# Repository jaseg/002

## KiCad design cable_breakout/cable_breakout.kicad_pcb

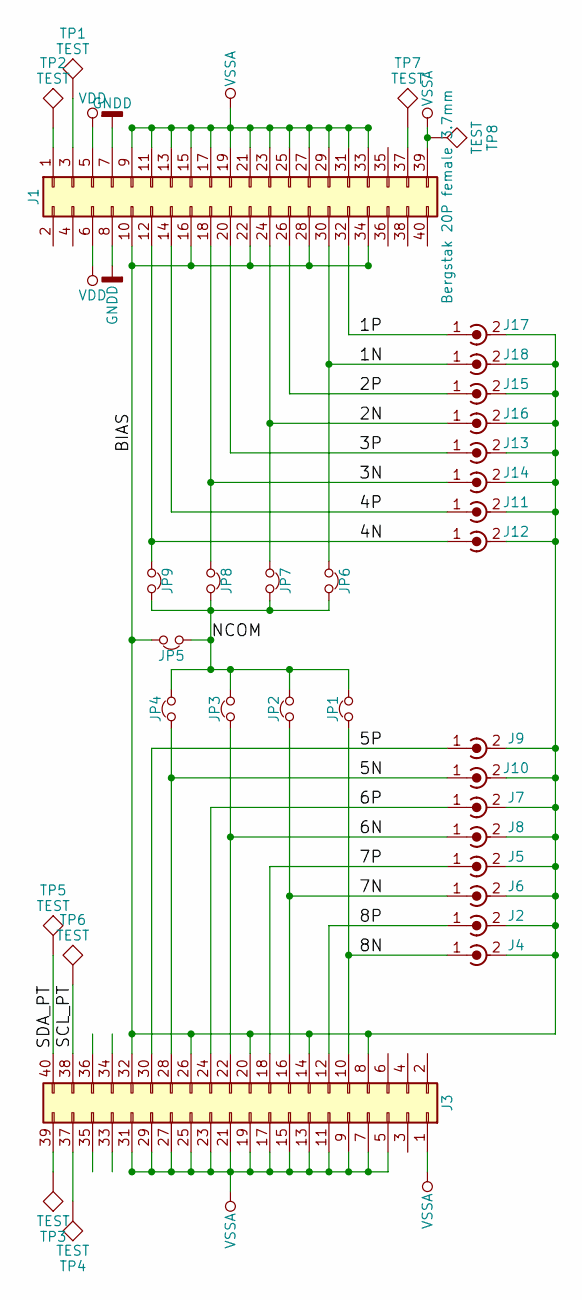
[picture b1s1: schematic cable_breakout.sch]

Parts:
J1: Bergstak 20P female 3.7mm; bergstak_plug_2x20_male; Mfg PN 10144517-041802LF; Digikey PN 609-5429-1-ND
J2, J4, J5, J6, J7, J8, J9, J10, J11, J12, J13, J14, J15, J16, J17, J18: Conn_Coaxial_Power; rg178_coax_solder_pad
J3: Conn_02x20_Odd_Even; bergstak_plug_2x20_male; Mfg PN 10144517-041802LF; Digikey PN 609-5429-1-ND
JP1, JP2, JP3, JP4, JP5, JP6, JP7, JP8, JP9: Jumper_NC_Small; solder_jumper_2pin
TP1, TP2, TP3, TP4, TP5, TP6, TP7, TP8: TEST; patch_pad

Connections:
/1N: J1.30, J18.1 (In), JP6.1
/1P: J1.32, J17.1 (In)
/2N: J1.24, J16.1 (In), JP7.1
/2P: J1.26, J15.1 (In)
/3N: J1.18, J14.1 (In), JP8.1
/3P: J1.20, J13.1 (In)
/4N: J1.12, J12.1 (In), JP9.1
/4P: J1.14, J11.1 (In)
/5N: J3.28, J10.1 (In), JP4.1
/5P: J3.30, J9.1 (In)
/6N: J3.22, J8.1 (In), JP3.1
/6P: J3.24, J7.1 (In)
/7N: J3.16, J6.1 (In), JP2.1
/7P: J3.18, J5.1 (In)
/8N: J3.10, J4.1 (In), JP1.1
/8P: J2.1 (In), J3.12
/BIAS: J1.10, J1.16, J1.22, J1.28, J1.34, J2.2 (Ext), J3.8, J3.14, J3.20, J3.26, J3.32, J4.2 (Ext), J5.2 (Ext), J6.2 (Ext), J7.2 (Ext), J8.2 (Ext), J9.2 (Ext), J10.2 (Ext), J11.2 (Ext), J12.2 (Ext), J13.2 (Ext), J14.2 (Ext), J15.2 (Ext), J16.2 (Ext), J17.2 (Ext), J18.2 (Ext), JP5.2
/NCOM: JP1.2, JP2.2, JP3.2, JP4.2, JP5.1, JP6.2, JP7.2, JP8.2, JP9.2
/SCL_PT: J3.38, TP6.1
/SDA_PT: J3.40, TP5.1
GNDD: J1.7, J1.8; also elsewhere on the board
unnamed: J1.1, TP2.1
unnamed: J1.3, TP1.1
unnamed: J1.37, TP7.1
unnamed: J3.37, TP4.1
unnamed: J3.39, TP3.1
VDD: J1.5, J1.6; also elsewhere on the board
VSSA: J1.9, J1.11, J1.13, J1.15, J1.17, J1.19, J1.21, J1.23, J1.25, J1.27, J1.29, J1.31, J1.33, J1.39, J3.1, J3.5, J3.7, J3.9, J3.11, J3.13, J3.15, J3.17, J3.19, J3.21, J3.23, J3.25, J3.27, J3.29, J3.31, TP8.1

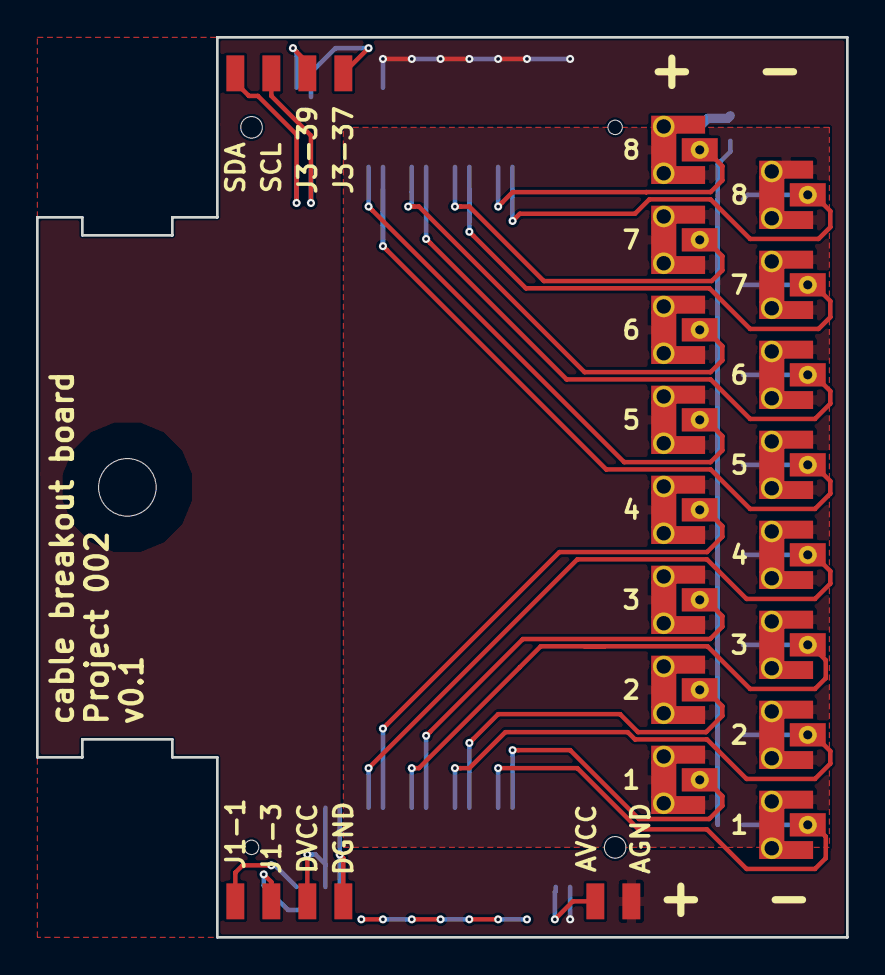
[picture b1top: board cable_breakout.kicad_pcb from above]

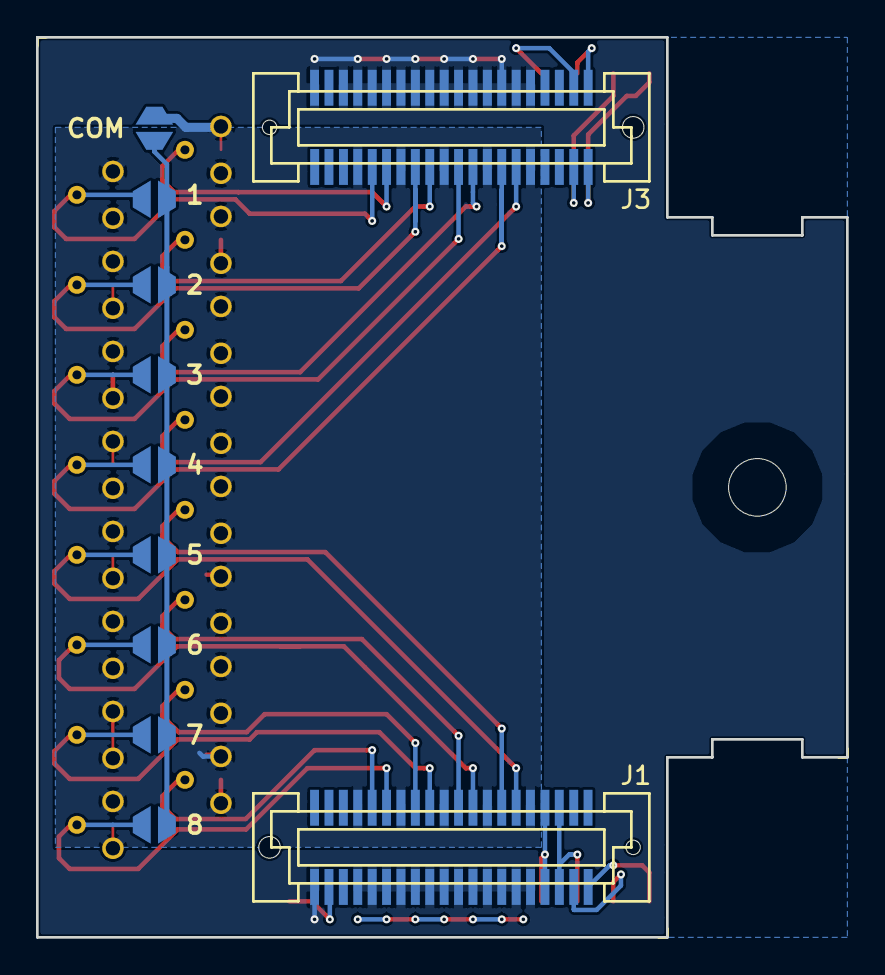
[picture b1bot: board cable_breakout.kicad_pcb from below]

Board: 2 copper layers, 45.0 x 50.0 mm, 37 parts (11 on the bottom side), 28 nets.

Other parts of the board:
TP9, TP10: TEST; patch_pad

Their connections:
GNDD: TP9.1; also elsewhere on the board
VDD: TP10.1; also elsewhere on the board

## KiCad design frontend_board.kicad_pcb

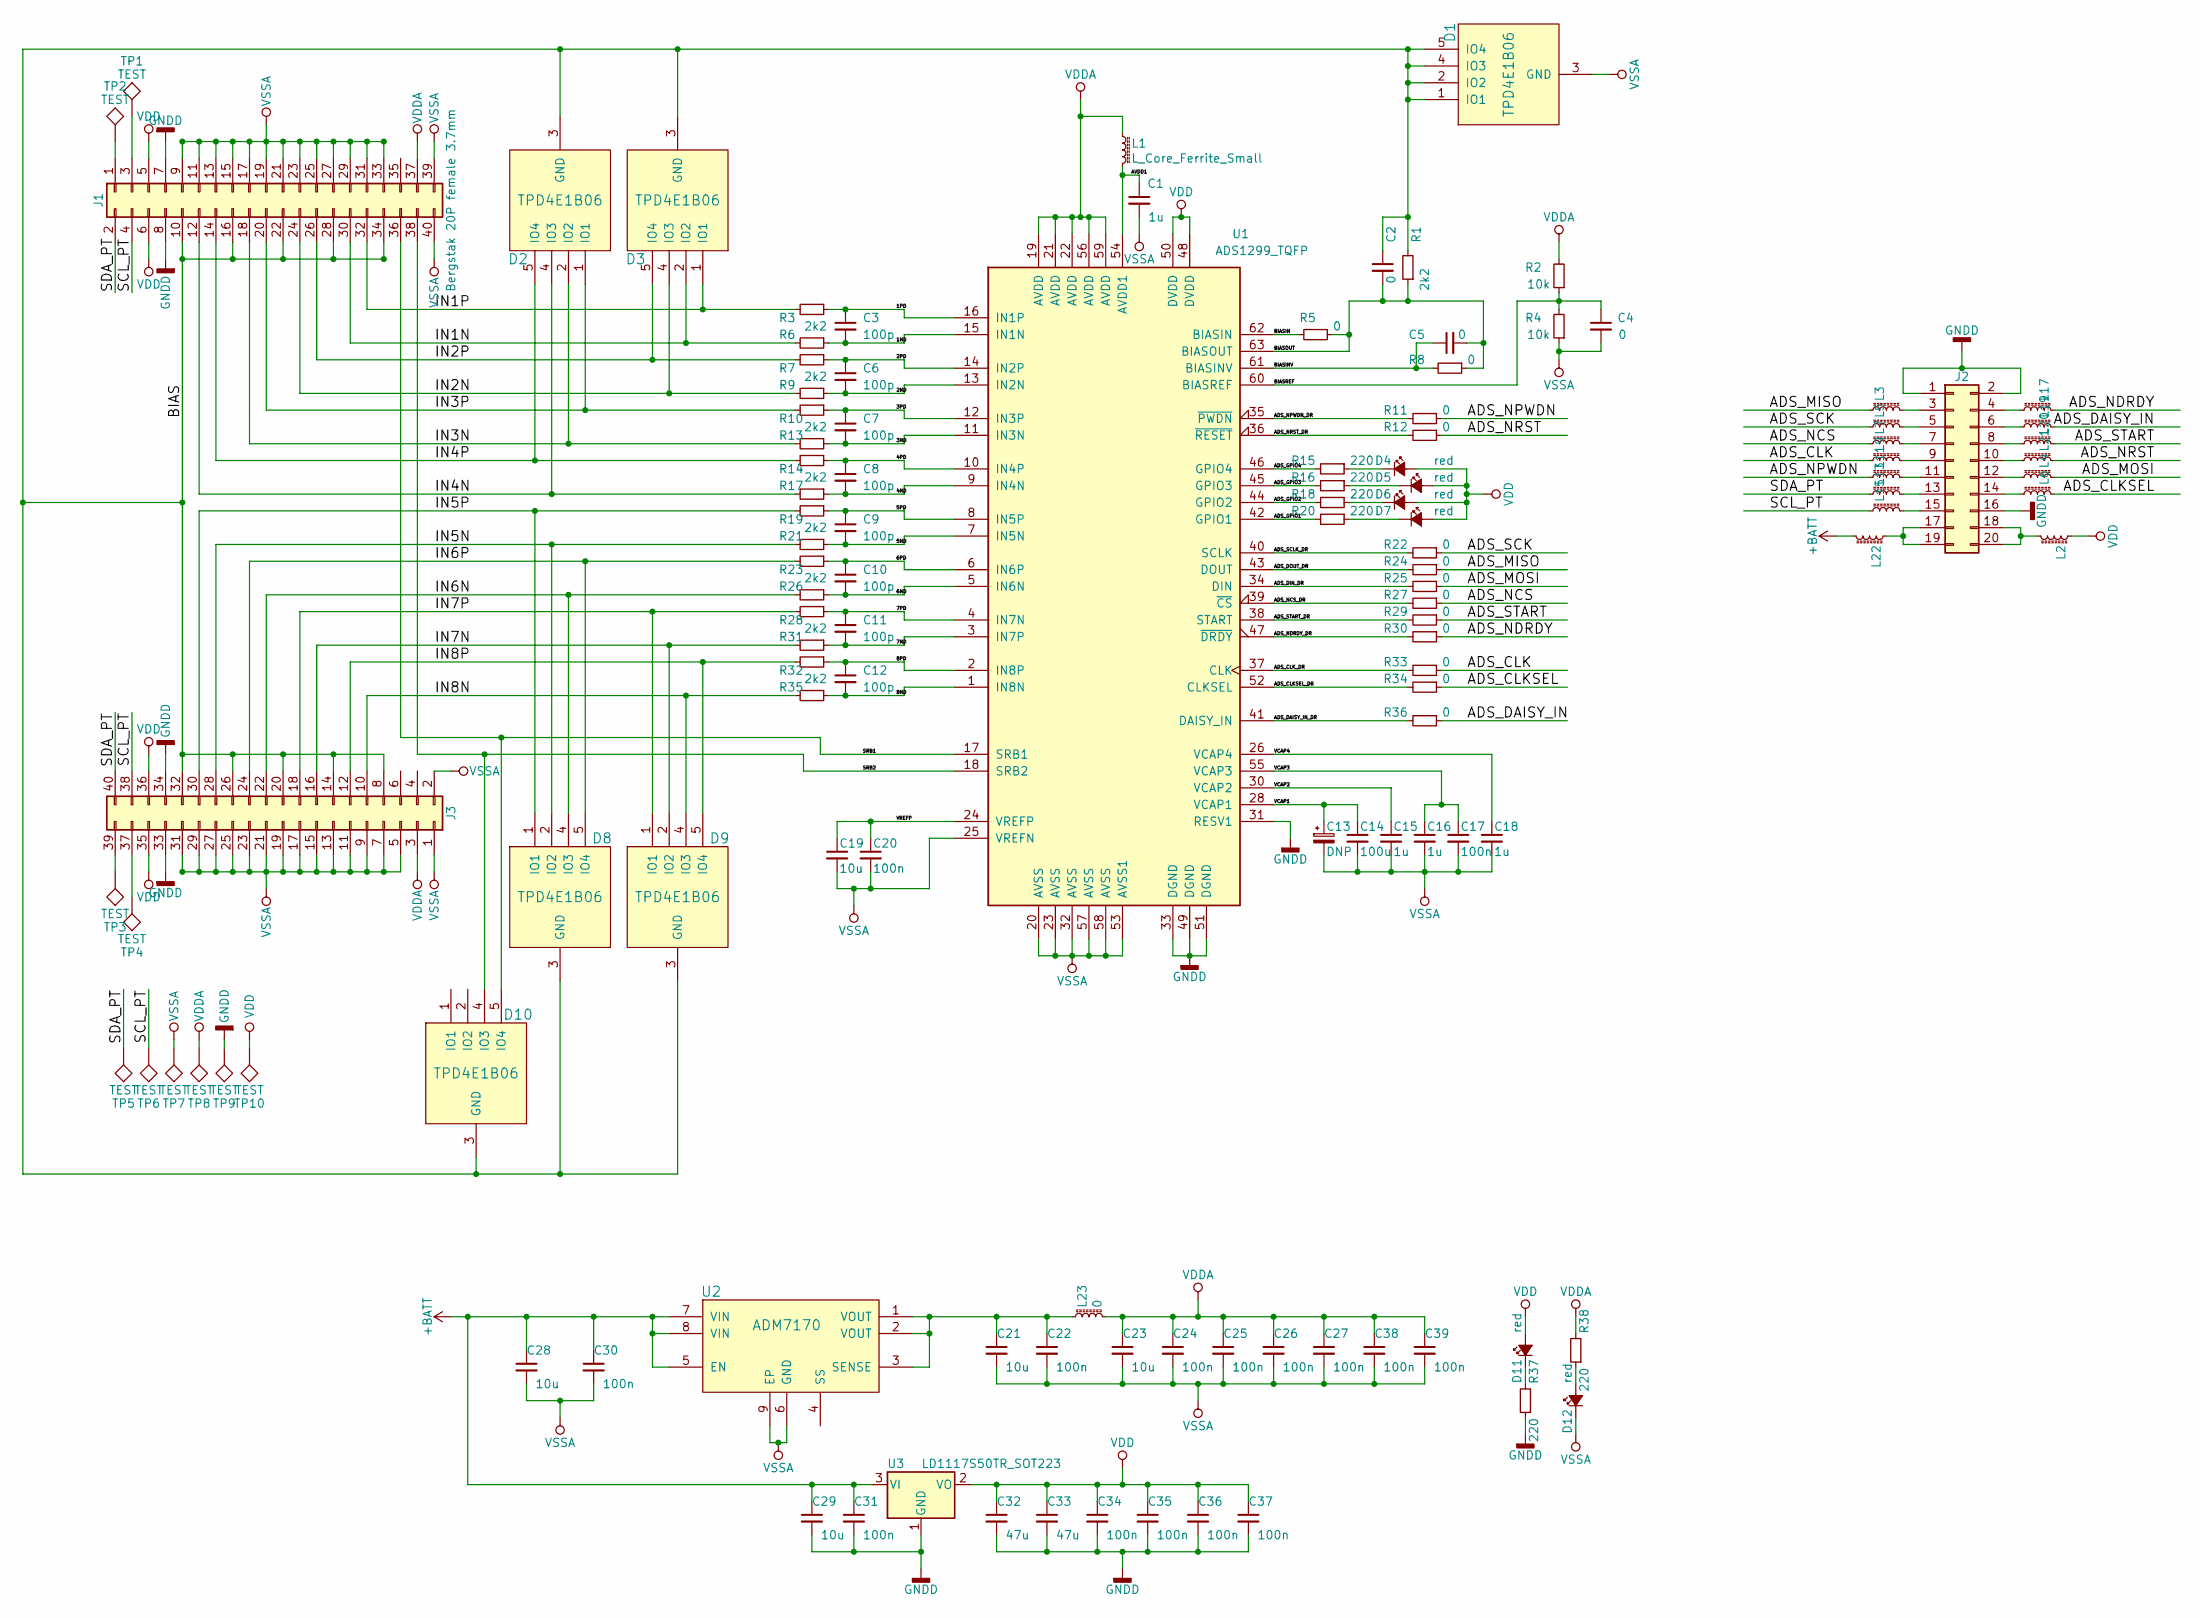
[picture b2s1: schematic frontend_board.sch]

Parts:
C1, C15, C16, C18: 1u; C_0402
C2, C4, C5: 0; C_0402
C3, C6, C7, C8, C9, C10, C11, C12: 100p; C_0402_NoSilk
C13: DNP; C_0402
C14: 100u; C_1210
C17, C20, C22, C24, C25, C26, C27, C30, C31, C34, C35, C36, C37, C38, C39: 100n; C_0402
C19, C21, C23, C28, C29: 10u; C_0603
C32, C33: 47u; C_0603
D1, D10: TPD4E1B06; SOT-363_SC-70-6
D2, D3, D8, D9: TPD4E1B06; SOT-363_SC-70-6-nosilk
D4, D5, D6, D7, D11, D12: red; LED_0603_HandSoldering
J1: Bergstak 20P female 3.7mm; bergstak_receptacle1_2x20_female; Mfg PN 10144517-041802LF; Digikey PN 609-5429-1-ND
J2: Conn_02x10_Odd_Even; Pin_Header_Straight_2x10_Pitch2.54mm_SMD
J3: Conn_02x20_Odd_Even; bergstak_receptacle1_2x20_female; Mfg PN 10144517-041802LF; Digikey PN 609-5429-1-ND
L1, L2, L3, L4, L5, L6, L7, L9, L11, L13, L15, L17, L19, L20, L21, L22: L_Core_Ferrite_Small; R_0402
L23: 0; R_0402
R1, R3, R6, R7, R9, R10, R13, R14, R17, R19, R21, R23, R26, R28, R31, R32, R35: 2k2; R_0402
R2, R4: 10k; R_0402
R5, R8, R11, R12, R22, R24, R25, R27, R29, R30, R33, R34, R36: 0; R_0402
R15, R16, R18, R20, R37, R38: 220; R_0402
TP1, TP2, TP3, TP4, TP5, TP6, TP7, TP8, TP9, TP10: TEST; patch_pad
U1: ADS1299_TQFP; TQFP-64_10x10mm_Pitch0.5mm
U2: ADM7170; SOIC-8_3.9x4.9mm_Pitch1.27mm
U3: LD1117S50TR_SOT223; SOT-223-3Lead_TabPin2

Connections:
+BATT: C28.1, C29.1, C30.1, C31.1, L22.2, U2.5 (EN), U2.7 (VIN), U2.8 (VIN), U3.3 (VI)
/1ND: C3.2, R6.1, U1.15 (IN1N)
/1PD: C3.1, R3.1, U1.16 (IN1P)
/2ND: C6.2, R9.1, U1.13 (IN2N)
/2PD: C6.1, R7.1, U1.14 (IN2P)
/3ND: C7.2, R13.1, U1.11 (IN3N)
/3PD: C7.1, R10.1, U1.12 (IN3P)
/4ND: C8.2, R17.1, U1.9 (IN4N)
/4PD: C8.1, R14.1, U1.10 (IN4P)
/5ND: C9.2, R21.1, U1.7 (IN5N)
/5PD: C9.1, R19.1, U1.8 (IN5P)
/6ND: C10.2, R26.1, U1.5 (IN6N)
/6PD: C10.1, R23.1, U1.6 (IN6P)
/7ND: C11.2, R31.1, U1.3 (IN7P)
/7PD: C11.1, R28.1, U1.4 (IN7N)
/8ND: C12.2, R35.1, U1.1 (IN8N)
/8PD: C12.1, R32.1, U1.2 (IN8P)
/ADS_CLK: L9.1, R33.1
/ADS_CLKSEL: L6.1, R34.1
/ADS_CLKSEL_DR: R34.2, U1.52 (CLKSEL)
/ADS_CLK_DR: R33.2, U1.37 (CLK)
/ADS_DAISY_IN: L19.1, R36.1
/ADS_DAISY_IN_DR: R36.2, U1.41 (DAISY_IN)
/ADS_DIN_DR: R25.2, U1.34 (DIN)
/ADS_DOUT_DR: R24.2, U1.43 (DOUT)
/ADS_GPIO1: R20.2, U1.42 (GPIO1)
/ADS_GPIO2: R18.2, U1.44 (GPIO2)
/ADS_GPIO3: R16.2, U1.45 (GPIO3)
/ADS_GPIO4: R15.2, U1.46 (GPIO4)
/ADS_MISO: L3.1, R24.1
/ADS_MOSI: L4.1, R25.1
/ADS_NCS: L7.1, R27.1
/ADS_NCS_DR: R27.2, U1.39 (~CS)
/ADS_NDRDY: L17.1, R30.1
/ADS_NDRDY_DR: R30.2, U1.47 (~DRDY)
/ADS_NPWDN: L11.1, R11.1
/ADS_NPWDN_DR: R11.2, U1.35 (~PWDN)
/ADS_NRST: L21.1, R12.1
/ADS_NRST_DR: R12.2, U1.36 (~RESET)
/ADS_SCK: L5.1, R22.1
/ADS_SCLK_DR: R22.2, U1.40 (SCLK)
/ADS_START: L20.1, R29.1
/ADS_START_DR: R29.2, U1.38 (START)
/AVDD1: C1.1, L1.2, U1.54 (AVDD1)
/BIAS: C2.1, D1.1 (IO1), D1.2 (IO2), D1.4 (IO3), D1.5 (IO4), D2.3 (GND), D3.3 (GND), D8.3 (GND), D9.3 (GND), D10.3 (GND), J1.10, J1.16, J1.22, J1.28, J1.34, J3.8, J3.14, J3.20, J3.26, J3.32, R1.2
/BIASIN: R5.2, U1.62 (BIASIN)
/BIASINV: C5.1, R8.2, U1.61 (BIASINV)
/BIASOUT: C2.2, C5.2, R1.1, R5.1, R8.1, U1.63 (BIASOUT)
/BIASREF: C4.1, R2.1, R4.2, U1.60 (BIASREF)
/IN1N: D3.2 (IO2), J1.30, R6.2
/IN1P: D3.1 (IO1), J1.32, R3.2
/IN2N: D3.4 (IO3), J1.24, R9.2
/IN2P: D3.5 (IO4), J1.26, R7.2
/IN3N: D2.2 (IO2), J1.18, R13.2
/IN3P: D2.1 (IO1), J1.20, R10.2
/IN4N: D2.4 (IO3), J1.12, R17.2
/IN4P: D2.5 (IO4), J1.14, R14.2
/IN5N: D8.2 (IO2), J3.28, R21.2
/IN5P: D8.1 (IO1), J3.30, R19.2
/IN6N: D8.4 (IO3), J3.22, R26.2
/IN6P: D8.5 (IO4), J3.24, R23.2
/IN7N: D9.2 (IO2), J3.16, R31.2
/IN7P: D9.1 (IO1), J3.18, R28.2
/IN8N: D9.4 (IO3), J3.10, R35.2
/IN8P: D9.5 (IO4), J3.12, R32.2
/SCL_PT: J1.4, J3.38, L15.1, TP6.1
/SDA_PT: J1.2, J3.40, L13.1, TP5.1
/SRB1: D10.5 (IO4), J1.36, U1.17 (SRB1)
/SRB2: D10.4 (IO3), J1.38, U1.18 (SRB2)
/VCAP1: C13.1, C14.1, U1.28 (VCAP1)
/VCAP2: C15.1, U1.30 (VCAP2)
/VCAP3: C16.1, C17.1, U1.55 (VCAP3)
/VCAP4: C18.1, U1.26 (VCAP4)
/VREFP: C19.1, C20.1, U1.24 (VREFP)
GNDD: C29.2, C31.2, C32.2, C33.2, C34.2, C35.2, C36.2, C37.2, J1.7, J1.8, J2.1, J2.2, J2.16, J3.33, J3.34, R37.1, TP9.1, U1.31 (RESV1), U1.33 (DGND), U1.49 (DGND), U1.51 (DGND), U3.1 (GND)
unnamed: C21.1, C22.1, L23.1, U2.1 (VOUT), U2.2 (VOUT), U2.3 (SENSE)
unnamed: D4.1 (K), R15.1
unnamed: D5.1 (K), R16.1
unnamed: D6.1 (K), R18.1
unnamed: D7.1 (K), R20.1
unnamed: D11.1 (K), R37.2
unnamed: D12.2 (A), R38.1
unnamed: J1.1, TP2.1
unnamed: J1.3, TP1.1
unnamed: J2.3, L3.2
unnamed: J2.4, L17.2
unnamed: J2.5, L5.2
unnamed: J2.6, L19.2
unnamed: J2.7, L7.2
unnamed: J2.8, L20.2
unnamed: J2.9, L9.2
unnamed: J2.10, L21.2
unnamed: J2.11, L11.2
unnamed: J2.12, L4.2
unnamed: J2.13, L13.2
unnamed: J2.14, L6.2
unnamed: J2.15, L15.2
unnamed: J2.17, J2.19, L22.1
unnamed: J2.18, J2.20, L2.2
unnamed: J3.37, TP4.1
unnamed: J3.39, TP3.1
VDD: C32.1, C33.1, C34.1, C35.1, C36.1, C37.1, D4.2 (A), D5.2 (A), D6.2 (A), D7.2 (A), D11.2 (A), J1.5, J1.6, J3.35, J3.36, L2.1, TP10.1, U1.48 (DVDD), U1.50 (DVDD), U3.2 (VO)
VDDA: C23.1, C24.1, C25.1, C26.1, C27.1, C38.1, C39.1, J1.37, J3.3, L1.1, L23.2, R2.2, R38.2, TP8.1, U1.19 (AVDD), U1.21 (AVDD), U1.22 (AVDD), U1.56 (AVDD), U1.59 (AVDD)
VSSA: C1.2, C4.2, C13.2, C14.2, C15.2, C16.2, C17.2, C18.2, C19.2, C20.2, C21.2, C22.2, C23.2, C24.2, C25.2, C26.2, C27.2, C28.2, C30.2, C38.2, C39.2, D1.3 (GND), D12.1 (K), J1.9, J1.11, J1.13, J1.15, J1.17, J1.19, J1.21, J1.23, J1.25, J1.27, J1.29, J1.31, J1.33, J1.39, J1.40, J3.1, J3.2, J3.5, J3.7, J3.9, J3.11, J3.13, J3.15, J3.17, J3.19, J3.21, J3.23, J3.25, J3.27, J3.29, J3.31, R4.1, TP7.1, U1.20 (AVSS), U1.23 (AVSS), U1.25 (VREFN), U1.32 (AVSS), U1.53 (AVSS1), U1.57 (AVSS), U1.58 (AVSS), U2.6 (GND), U2.9 (EP)

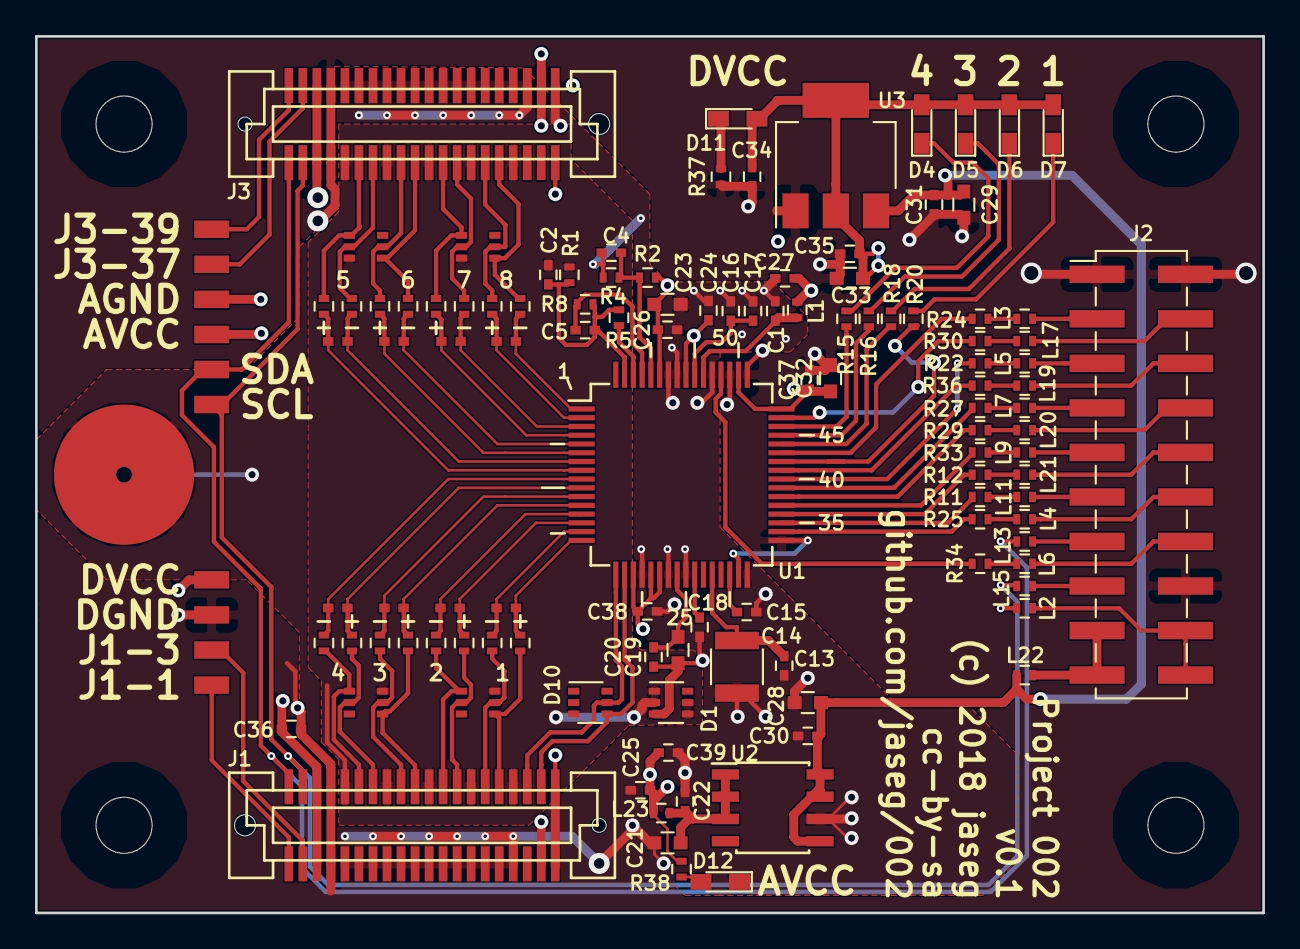
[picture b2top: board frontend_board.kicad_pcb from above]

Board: 4 copper layers, 70.0 x 50.0 mm, 122 parts (0 on the bottom side), 104 nets.

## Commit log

2018-06-30 frontend: Reshape to 60x70mm, fixup silk
2018-07-01 Add cable breakout board
2018-07-01 Reorg boards into subdirs
2018-11-27 Do proper pretty breakout gerber export
2018-11-27 Add pretty frontend gerber export

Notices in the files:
frontend_board.kicad_pcb:
(c) 2018 jaseg
cc-by-sa
